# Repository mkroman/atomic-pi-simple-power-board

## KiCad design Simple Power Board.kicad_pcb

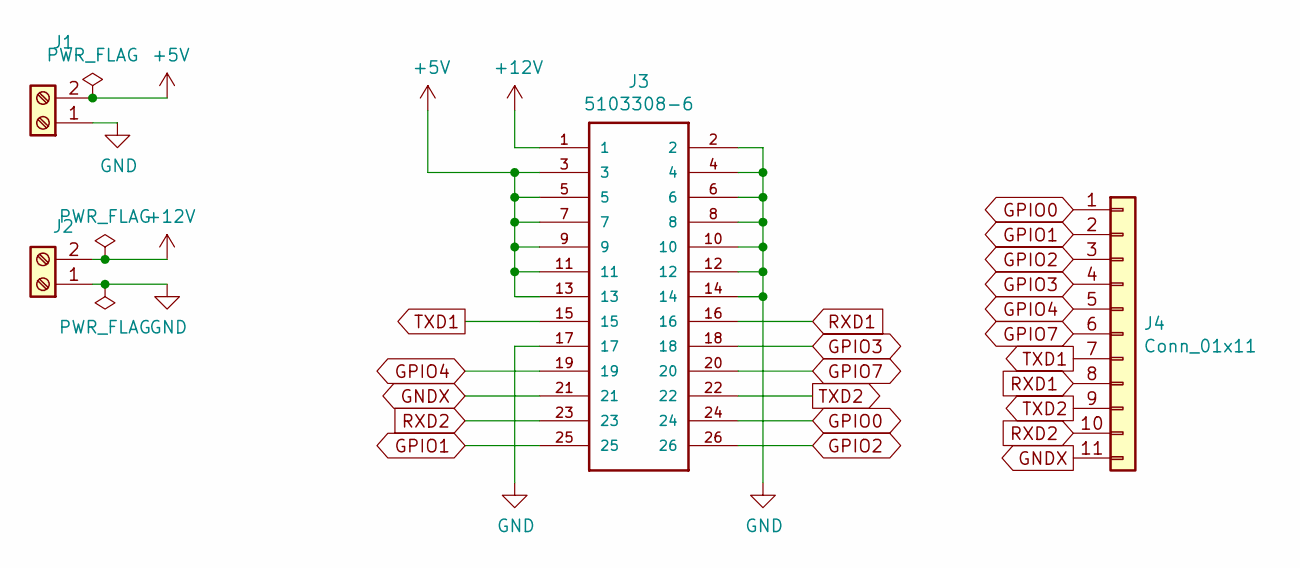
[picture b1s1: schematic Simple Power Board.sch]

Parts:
J1, J2: Screw_Terminal_01x02; TerminalBlock_Phoenix_PT-1,5-2-5.0-H_1x02_P5.00mm_Horizontal
J3: 5103308-6; TE_5103308-6
J4: Conn_01x11; PinHeader_1x12_P2.54mm_Vertical

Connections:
+5V: J1.2, J3.3, J3.5, J3.7, J3.9, J3.11, J3.13
+12V: J2.2, J3.1
GND: J1.1, J2.1, J3.2, J3.4, J3.6, J3.8, J3.10, J3.12, J3.14, J3.17
GNDX: J3.21, J4.11
GPIO0: J3.24, J4.1
GPIO1: J3.25, J4.2
GPIO2: J3.26, J4.3
GPIO3: J3.18, J4.4
GPIO4: J3.19, J4.5
GPIO7: J3.20, J4.6
RXD1: J3.16, J4.8
RXD2: J3.23, J4.10
TXD1: J3.15, J4.7
TXD2: J3.22, J4.9

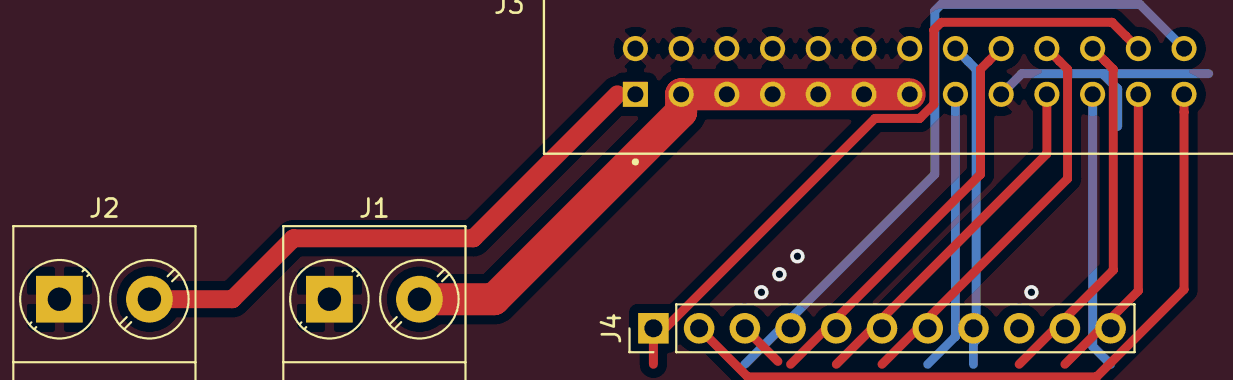
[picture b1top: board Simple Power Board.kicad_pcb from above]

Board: 2 copper layers, 4 parts (0 on the bottom side), 14 nets.
